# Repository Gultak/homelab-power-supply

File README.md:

# Rack power board: separate 12 V and 54 V supplies

Power distribution board for a 3D-printed 1U 10" rack case with **two** Mean Well supplies:
a LOP-300-54 for 54 V and a **LOP-200-12 or LOP-300-12** for 12 V. There is no DC-DC brick;
5 V comes from a Pololu D24V90F5 step-down module fed from the 12 V supply.

| Output | Connector | Protection | Rating |
|---|---|---|---|
| 54 V IN | J1 (6-pin JST VH, left edge, top end) | — (LOP-300-54's own protection) | from LOP-300-54 |
| 12 V IN | J10 (6-pin JST VH, right edge, top end) | — | from LOP-200-12 / LOP-300-12 |
| 54 V OUT 1 / 2 | J2, J3 (screw terminals, left edge, bottom end) | F2, F3 5×20 T 2.5 A | 2 A each |
| 5 V OUT | J8 (screw terminal, bottom edge) | F8 ATM 5 A on the Pololu's 12 V feed; Pololu current limit | 6 A, **shared with J9** |
| 12 V OUT 1–4 | J4–J7 (screw terminals, bottom edge) | F4–F7 ATM mini blade (5 A, or 3 A per load) | 3–5 A each |
| 5 V AUX | J9 (4-pin Molex 8981, top edge, far left) | same as J8 | pinout **+5V, GND, GND, +5V** |

* **Board:** 83.2 × 80.0 mm, 2 layers, **2 oz copper**, 1.6 mm. 4× M3 holes, 9 mm Ø
  copper keep-out around each.
* **Outputs** are 2-pin 5.08 mm screw terminals (YE0001XC321 or any 5.08 mm block that fits
  the Phoenix MKDS-1,5 footprint: 1.3 mm holes, body 10.16 × 9.8 mm), with the wire entry
  flush with the board edge. Each output has its own + and GND screw (no shared grounds).
  * **Bottom edge**, left to right: **5V, 12V 1, 12V 2, 12V 3, 12V 4**, side by side at
    10.3 mm pitch. The left screw of each block (marked `+`) is positive.
  * **Left edge**, as low as the corner mounting hole allows: **54V 1** (upper) and **54V 2**
    (lower), wires entering from the left. The upper screw of each block (marked `+`) is
    positive.
  * Screw terminals have no polarity keying: go by the `+`/`−` marks next to each block
    (also printed on the bottom). Use ferrules on stranded wire.
  * With 5 V next to the 54 V block, no supply rail has to cross another one.
* **Inputs:** J1 (54 V) on the left edge and J10 (12 V) on the right edge, both at the top
  end, so each sits next to its own PSU. Both are B6P-VH headers, plugs entering from above. On both,
  pins 1–3 (top, next to the ▽ mark) are **+** and pins 4–6 are **GND**. Three contacts per
  pole give 30 A. Make both cables with a **VHR-6N** housing, SVH-41T-P1.1 contacts and
  1.25 mm² (AWG 16) wire, and use all six wires. Check each LOP's own output connector in
  its datasheet for the other end of the cable. Label the two cables: they use the same
  connector and swapping them would put 54 V on the 12 V side.
* **54 V is a fused passthrough** with its **own ground (GND54)**. The whole left column
  below J9 is the 54 V block: J1 feeds F2/F3 and J2/J3 through a +54 V copper pour on the
  top layer, and the bottom layer there is GND54, with a 1.5 mm gap to the 12 V/5 V ground.
  Nothing on the 12 V/5 V side connects to it, and there is no option to tie the two
  grounds (the two LOP supplies have isolated outputs).
* **5 V:** a Pololu D24V90F5, lying horizontally between the two inputs and
  soldered flat to the board, with no standoffs and no wires (VOUT end left, VIN end right). A
  +5 V copper pour feeds J9 above and J8 below.
  * **Header pins (mechanical):** at each end, a 4-pin straight 0.1" male header goes
    through the Pololu's row of 4 small holes and the matching holes in this board. Per
    Pololu's drawing the small holes are Ø1.02 mm; this board has Ø1.0 mm holes.
  * **Wire links (current):** at each end, a short piece of solid copper wire goes through
    each of the two large terminal-block holes (VIN or VOUT, and GND) into this board's
    Ø1.6 mm holes. Use the thickest solid wire that fits the Pololu's holes. These links
    carry the 6 A; the 0.1" pins alone are not meant for it.
  * **Gap:** at least 2.5 mm, which is one standard header spacer. About 5 mm (two
    spacers, extra-long header pins) gives better airflow underneath. There are no
    components under the Pololu, only copper under solder mask.
  * **Orientation:** component side up, with the VOUT end on the left and the FB/PG/EN pin
    column towards the front (output) edge of this board. The silkscreen marks the VIN and
    VOUT ends and the FB/PG/EN side.
  * **Pinout:** taken from Pololu's dimension drawing. The FB/PG/EN column sits nearer the
    VIN end, and at both ends the large GND hole is on the column side. Check this against
    the labels on the back of your Pololu before soldering.
* **J9** sits on the top edge as far left as the corner mounting hole allows (pin 1 at
  15.3 mm). The right-angle plug enters from the top edge.
* **J9 warning:** its pinout (+5V, GND, GND, +5V) is **not** the PC standard (+12V, GND,
  GND, +5V). Never plug a PC PSU's peripheral cable into it.
* **Status LEDs** are 2-pin 2.54 mm headers (D2 = 54 V, D3 = 12 V, D4 = 5 V), so the LEDs
  can sit in the case front and connect with female Dupont leads. Pin 1 (marked `+`) is
  the LED anode, already behind its series resistor (R1–R3 stay on the board); pin 2 is
  GND (GND54 for D2). The resistors set about 10 mA for a plain red LED without a built-in resistor (Lumex SSI-LXMP059ID panel-mount LEDs). A header with a Dupont
  housing on it is about 14 mm tall, a mated VH input plug about 17 mm, and the screw
  terminals about 10 mm.

## Mounting holes

Coordinates are in mm from the board's **top-left corner**, as seen from the component
side, with the output connector edge at the bottom. X runs right and Y runs down. All
holes are unplated (NPTH).

| Hole | Purpose | X | Y | Drill | Notes |
|---|---|---|---|---|---|
| H1 | board mount | 4.00 | 4.00 | 3.2 mm (M3) | 9 mm Ø copper-free area on both sides |
| H2 | board mount | 79.20 | 4.00 | 3.2 mm (M3) | same |
| H3 | board mount | 4.00 | 75.50 | 3.2 mm (M3) | same |
| H4 | board mount | 79.20 | 75.50 | 3.2 mm (M3) | same |

* **Board outline:** 83.2 × 80.0 mm.
* **M3 pattern:** 75.2 × 71.5 mm centre-to-centre, inset 4 mm from the top, left and
  right edges and 4.5 mm from the output connector edge.

## Layout and copper

* **Top layer:** +54 V pour in the left column (J1 to F2/F3); +5 V pour along the top-left
  (J9), under the left half of the Pololu and down to J8; +12 V pour from J10 to F8, C5/C6,
  D3 and the 12 V fuses.
* **Bottom layer:** GND everywhere except the 54 V block (GND54).
* **Pad connections:** power pads join the pours solidly (no thermal reliefs). Use a hot
  iron (≥ 60 W) for J*, F* and the Pololu wire links.

## Bill of materials

For part numbers, order status and DigiKey Ireland part numbers and prices, see **[BOM.md](BOM.md)**.

## Power budget

* **12 V supply:** J4–J7 at 5 A each (20 A) plus the Pololu at 6 A × 5 V (about 2.8 A at
  12 V) adds up to about 23 A worst case. A LOP-300-12 (25 A) covers that. A LOP-200-12
  (16.7 A) is fine as long as the **actual** combined 12 V + 5 V load stays under 200 W.
* **54 V supply:** the LOP-300-54 now only feeds J2/J3 (2 × 2.5 A fuses), well under its
  5.6 A. Its own overload protection covers the J1 wiring, so there is no input fuse.

## Before ordering: check these

1. **J1/J10 cables:** confirm the output connector on both LOPs and make the cables to
   match. Keep the order (pins 1–3 +, 4–6 −) and mark which cable is 54 V.
2. **Pololu pinout:** check the VIN/GND/VOUT labels on the back of your Pololu against the VIN/VOUT
   marks on this board.
3. **J9 footprint:** the right-angle tab holes come from measurements of your own headers.
4. **Screw terminals:** check that your blocks fit the 1.3 mm holes at 5.08 mm pitch and are
   no wider than 10.3 mm, so the five on the bottom edge sit side by side.
5. **Fuse holders and blade holders:** they use the KiCad library footprints (Schurter
   0031.8201, Keystone 3568). Compare them against the parts you actually buy.

## Files

* `rack-power-board.kicad_pcb`: KiCad 9 board (board-only, nets assigned, no schematic).
* `rack-power-board-gerbers.zip`: gerbers and drill files. Upload as-is to JLCPCB/PCBWay
  and pick 2 oz copper.
* `docs/`: top and bottom renders, a top assembly PDF and the DRC report. The report has 0
  electrical violations and 0 unconnected items; the remaining entries are silkscreen
  overlaps and "library not configured" notices from generating the board by script.
* `build.py` / `post.py`: the generator scripts (KiCad 9 `pcbnew` Python). Run
  `python3 build.py && python3 post.py` to regenerate, fill zones and run DRC.
  They use the shared tools in the `tools/agent-tools` submodule
  ([Gultak/agent-tools](https://github.com/Gultak/agent-tools)): run
  `git submodule update --init` after cloning.
* `tools/bom_data.py` / `tools/gen_bom.py`: the parts list and the script that writes `BOM.md`
  and `digikey-bom.csv` from it.

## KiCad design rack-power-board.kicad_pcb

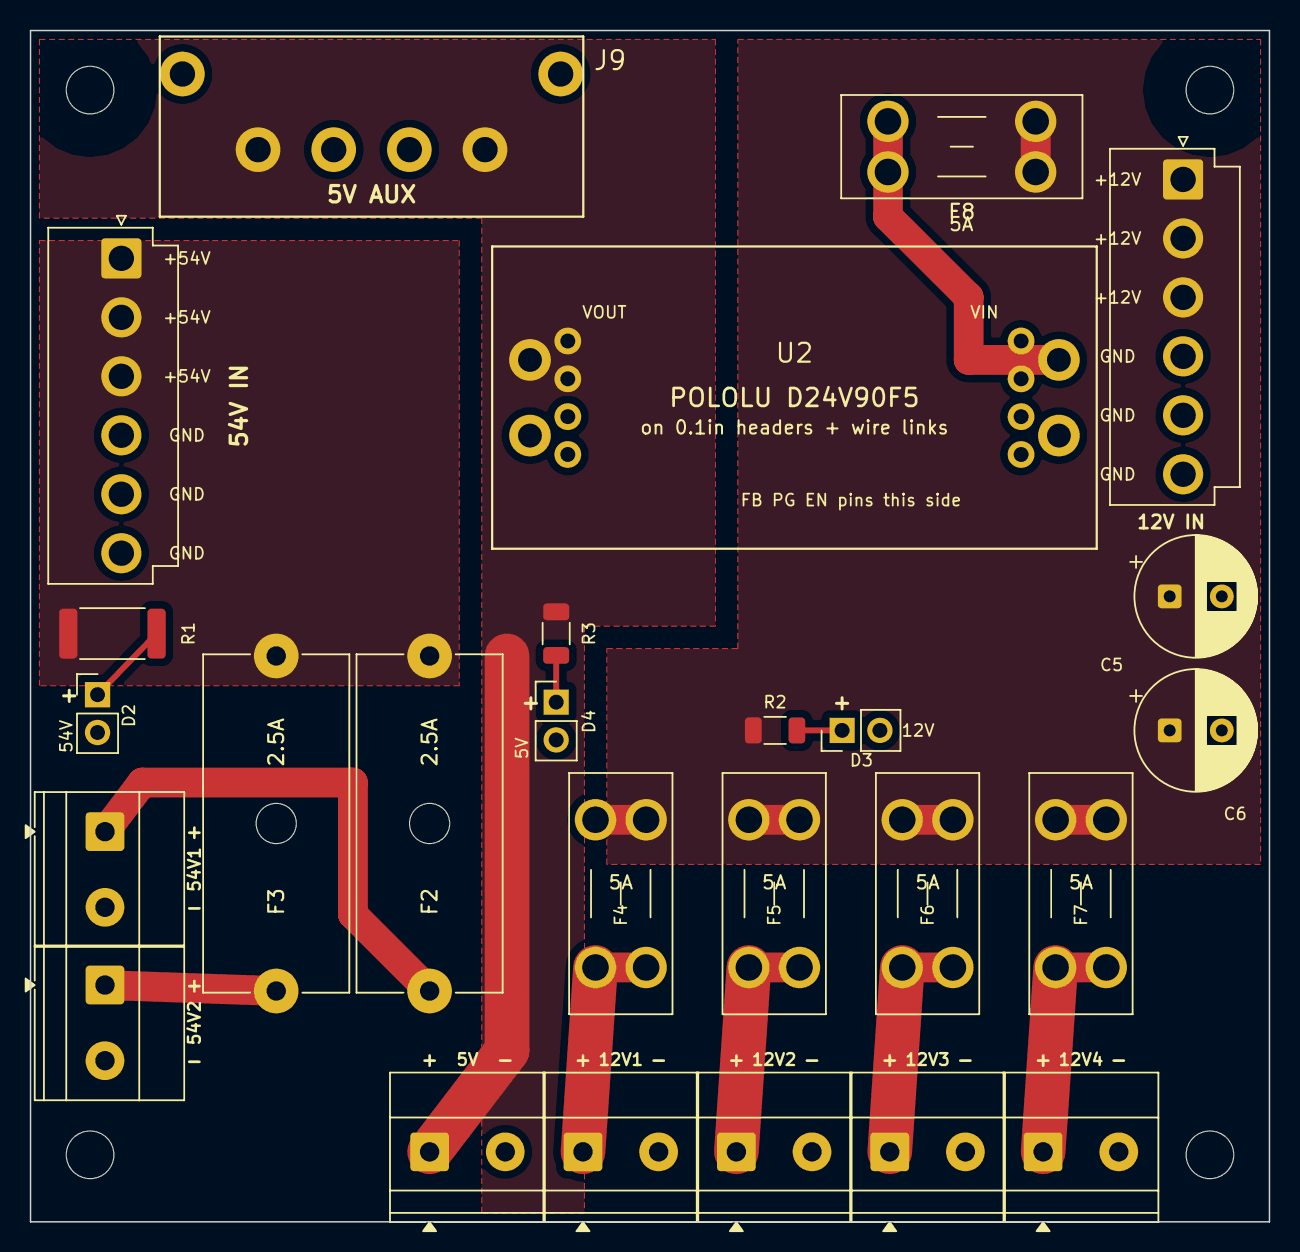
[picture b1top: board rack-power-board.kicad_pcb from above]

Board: 2 copper layers, 83.2 x 80.0 mm, 30 parts (0 on the bottom side), 15 nets.

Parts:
C5, C6: 470uF 16V polymer; CP_Radial_D8.0mm_P3.50mm
D2: LED 54V header; PinHeader_1x02_P2.54mm_Vertical
D3: LED 12V header; PinHeader_1x02_P2.54mm_Vertical
D4: LED 5V header; PinHeader_1x02_P2.54mm_Vertical
F2, F3: 5x20 T 2.5A; Fuseholder_Cylinder-5x20mm_Schurter_0031_8201_Horizontal_Op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
F4, F5, F6, F7, F8: ATM 5A; Fuseholder_Blade_Mini_Keystone_3568
H1, H2, H3, H4: M3; MountingHole_3.2mm_M3
J1, J10: JST B6P-VH; JST_VH_B6P-VH_1x06_P3.96mm_Vertical
J2, J3, J4, J5, J6, J7, J8: 5.08mm screw terminal 2p; TerminalBlock_Phoenix_MKDS-1,5-2-5.08_1x02_P5.08mm_Horizont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
J9: Molex_8981_1x04_P5.08mm_Horizontal
R1: 5.1k 1W; R_2512_6332Metric
R2: 1k; R_1206_3216Metric
R3: 300R; R_1206_3216Metric
U2: Pololu_D24V90F5_headers

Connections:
12V_PL: F8.2, U2.1, U2.3, U2.4
+5V: J8.1, J9.1, J9.4, R3.1, U2.7, U2.9, U2.10
+12V: C5.1, C6.1, F4.1, F5.1, F6.1, F7.1, F8.1, J10.1, J10.2, J10.3, R2.1
+54V: F2.1, F3.1, J1.1, J1.2, J1.3, R1.1
GND: C5.2, C6.2, D3.2, D4.2, J4.2, J5.2, J6.2, J7.2, J8.2, J9.2, J9.3, J9.MP, J10.4, J10.5, J10.6, U2.2, U2.5, U2.6, U2.8, U2.11, U2.12
GND54: D2.2, J1.4, J1.5, J1.6, J2.2, J3.2
LED5: D4.1, R3.2
LED12: D3.1, R2.2
LED54: D2.1, R1.2
OUT12_1: F4.2, J4.1
OUT12_2: F5.2, J5.1
OUT12_3: F6.2, J6.1
OUT12_4: F7.2, J7.1
OUT54_1: F2.2, J2.1
OUT54_2: F3.2, J3.1

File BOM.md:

# Bill of materials: rack power board

Quantities are for one board and include spare fuses. Prices are DigiKey Ireland line totals in EUR
including VAT, as checked in November 2026.

| Status | Meaning |
|---|---|
| 🛒 | Order from DigiKey Ireland |
| 🏠 | At hand |
| 🚚 | Ordered elsewhere, on the way |
| 🟩 | PCB, ordered from JLCPCB |

## Parts list

| Status | Ref | Qty | Part | Manufacturer | Part number | DigiKey part # | € inc. VAT |
|---|---|---|---|---|---|---|---|
| 🏠 | — | 1 | PSU 54 V, 300 W | Mean Well | LOP-300-54 | | |
| 🛒 | — | 1 | PSU 12 V, 300 W | Mean Well | LOP-300-12 | [1866-LOP-300-12-ND](https://www.digikey.ie/en/products/detail/mean-well-usa-inc/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 | 44.65 |
| 🟩 | PCB | 1 | 83.2 × 80 mm, 2 layers, 2 oz Cu, 1.6 mm | JLCPCB | `rack-power-board-gerbers.zip` | | |
| 🚚 | U2 | 1 | 5 V / 9 A step-down module | Pololu | D24V90F5 (#2866) | | |
| 🏠 | J1, J10 | 2 | Header, 6-pos, 3.96 mm, vertical | JST | B6P-VH | | |
| 🏠 | (J1/J10 plugs) | 2 | Crimp housing, 6-pos, 3.96 mm | JST | VHR-6N | | |
| 🏠 | (J1/J10 contacts) | 16 | Crimp contact, AWG 18–16 (12 + 4 spare) | JST | SVH-41T-P1.1 | | |
| 🏠 | J2–J8 | 7 | Screw terminal, 2-pos, 5.08 mm, horizontal entry | — | YE0001XC321 | | |
| 🏠 | J9 | 1 | 4-pin 5.08 mm disk-drive header, right-angle | Molex | 0015244441 (A-8981-4R-1-LF) | | |
| 🏠 | J9 (alternative) | 1 | 4-pin 5.08 mm disk-drive header, vertical | Molex | 0015244745 (A-8981-4V5-LF) | | |
| 🏠 | (J9 plug) | 1 | 4-pos disk-drive plug housing | Molex | 0015244048 (8981-04P) | | |
| 🏠 | (J9 plug contacts) | 4 | Female crimp contact for 8981 plug | Molex | 0008500113 (08-50-0113) | | |
| 🛒 | F2, F3 | 2 | 5×20 mm PCB fuse holder, open | Schurter | 0031.8201 | [486-1258-ND](https://www.digikey.ie/en/products/detail/schurter-inc/0031-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 | 2.98 |
| 🛒 | (F2/F3 covers) | 2 | Cover for 0031.8201 (optional) | Schurter | 0853.0551 | [486-1960-ND](https://www.digikey.ie/en/products/detail/schurter-inc/0853-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 | 2.36 |
| 🛒 | (F2/F3 fuses) | 4 | Fuse 5×20 mm, 2.5 A time-lag, 250 V (2 + 2 spare) | Littelfuse | 021802.5MXP | [F1751-ND](https://www.digikey.ie/en/products/detail/littelfuse-inc/021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 | 6.74 |
| 🛒 | F4–F8 | 5 | Mini blade (ATM) fuse holder, PCB | Keystone | 3568 | [36-3568-ND](https://www.digikey.ie/en/products/detail/keystone-electroni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 | 8.24 |
| 🛒 | (F4–F8 fuses) | 8 | ATM fuse, 5 A, 32 V (5 + 3 spare) | Littelfuse | 0297005.WXNV | [F989-ND](https://www.digikey.ie/en/products/detail/littelfuse-inc/029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 | 2.62 |
| 🏠 | (optional fuses) | 5 | ATM fuse, 3 A, 32 V | Littelfuse | 0297003.WXNV | | |
| 🛒 | C5, C6 | 2 | 470 µF 16 V aluminium polymer, Ø8 mm, 3.5 mm pitch | Panasonic | 16SEPG470M | [P122605-ND](https://www.digikey.ie/en/products/detail/panasonic-industry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 | 3.76 |
| 🛒 | R1 | 1 | 5.1 kΩ 1 %, 2512, 1 W | Yageo | RC2512FK-075K1L | [13-RC2512FK-075K1LCT-ND](https://www.digikey.ie/en/products/detail/yageo/RC2512FK-075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 | 0.38 |
| 🛒 | R2 | 1 | 1 kΩ 1 %, 1206 | Yageo | RC1206FR-071KL | [311-1.00KFRCT-ND](https://www.digikey.ie/en/products/detail/yageo/RC1206FR-071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 | 0.11 |
| 🛒 | R3 | 1 | 300 Ω 1 %, 1206 | Yageo | RC1206FR-07300RL | [311-300FRCT-ND](https://www.digikey.ie/en/products/detail/yageo/RC1206FR-073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 | 0.11 |
| 🏠 | D2–D4 | 3 | Pin header 1×2, 2.54 mm, vertical | Sullins | PREC002SAAN-RC | | |
| 🛒 | (case LEDs) | 3 | Panel-mount LED, 2 × 5 mm, red diffused, snap-in, no built-in resistor | Lumex | SSI-LXMP059ID | [67-1179-ND](https://www.digikey.ie/en/products/detail/lumex-opto-compone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 | 3.14 |
| 🏠 | (LED leads) | 3 | Dupont jumper, female–female, 2-pin | generic | 2.54 mm Dupont F-F | | |
| 🏠 | (U2 mount) | 2 | Pin header 1×4, 2.54 mm, straight (extra-long for a 5 mm gap) | generic | 0.1" male header | | |
| 🏠 | (U2 links) | ~10 cm | Solid copper wire, as thick as fits the Pololu's large holes | generic | e.g. 1.5 mm² solid | | |
| 🏠 | — | 4 | M3 heat-set insert | generic | M3 × 5.7 mm, OD 4.6 mm | | |
| 🏠 | — | 4 | M3 screw, pan head | generic | ISO 7045 M3 × 8 | | |
| 🛒 | — | 14+ | Wire ferrule, 1.0 mm² × 8 mm, red (DIN 46228-4) | Phoenix Contact | 3200030 (AI 1-8 RD) | [277-2188-ND](https://www.digikey.ie/en/products/detail/phoenix-contact/32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 | 2.76 |
| 🏠 | — | ~2 m | Wire 1.25 mm² (AWG 16): J1/J10 input cables from the PSUs | generic | H05V-K 1.5 mm² or AWG 16 silicone | | |
| 🏠 | — | as needed | Wire 1 mm² (AWG 18), red + black: output leads (12 V, 5 V) and 54 V Powerpole leads | generic | H05V-K 1.0 mm² or AWG 18 silicone | | |
| | **Total** | | **DigiKey order (🛒)** | | | | **77.85** |

## Notes

* **DigiKey upload:** [`digikey-bom.csv`](digikey-bom.csv) has the 🛒 lines with quantities and DigiKey part numbers, ready for the DigiKey cart or BOM Manager upload.
* **Use the cut-tape DigiKey numbers (`…CT-ND`)**, not tape and reel (`…TR-ND`). Tape and reel is sold only as full
  reels (4,000 pieces for the 2512).
* **R1 is a 1 W 2512.** A 1206 at that value would overheat: R1 dissipates about 0.53 W.
* **LEDs:** use the plain SSI-LXMP059ID, not the SSI-LXMP059ID5V150 variant, which has a resistor built in. Solder half
  a female–female Dupont lead to each LED.
* **J9:** fit one of the two headers, right-angle or vertical. The board has holes for both.
* **Delivery:** DigiKey Ireland delivers free from €92.25 inc. VAT; below that, delivery is about €25.
